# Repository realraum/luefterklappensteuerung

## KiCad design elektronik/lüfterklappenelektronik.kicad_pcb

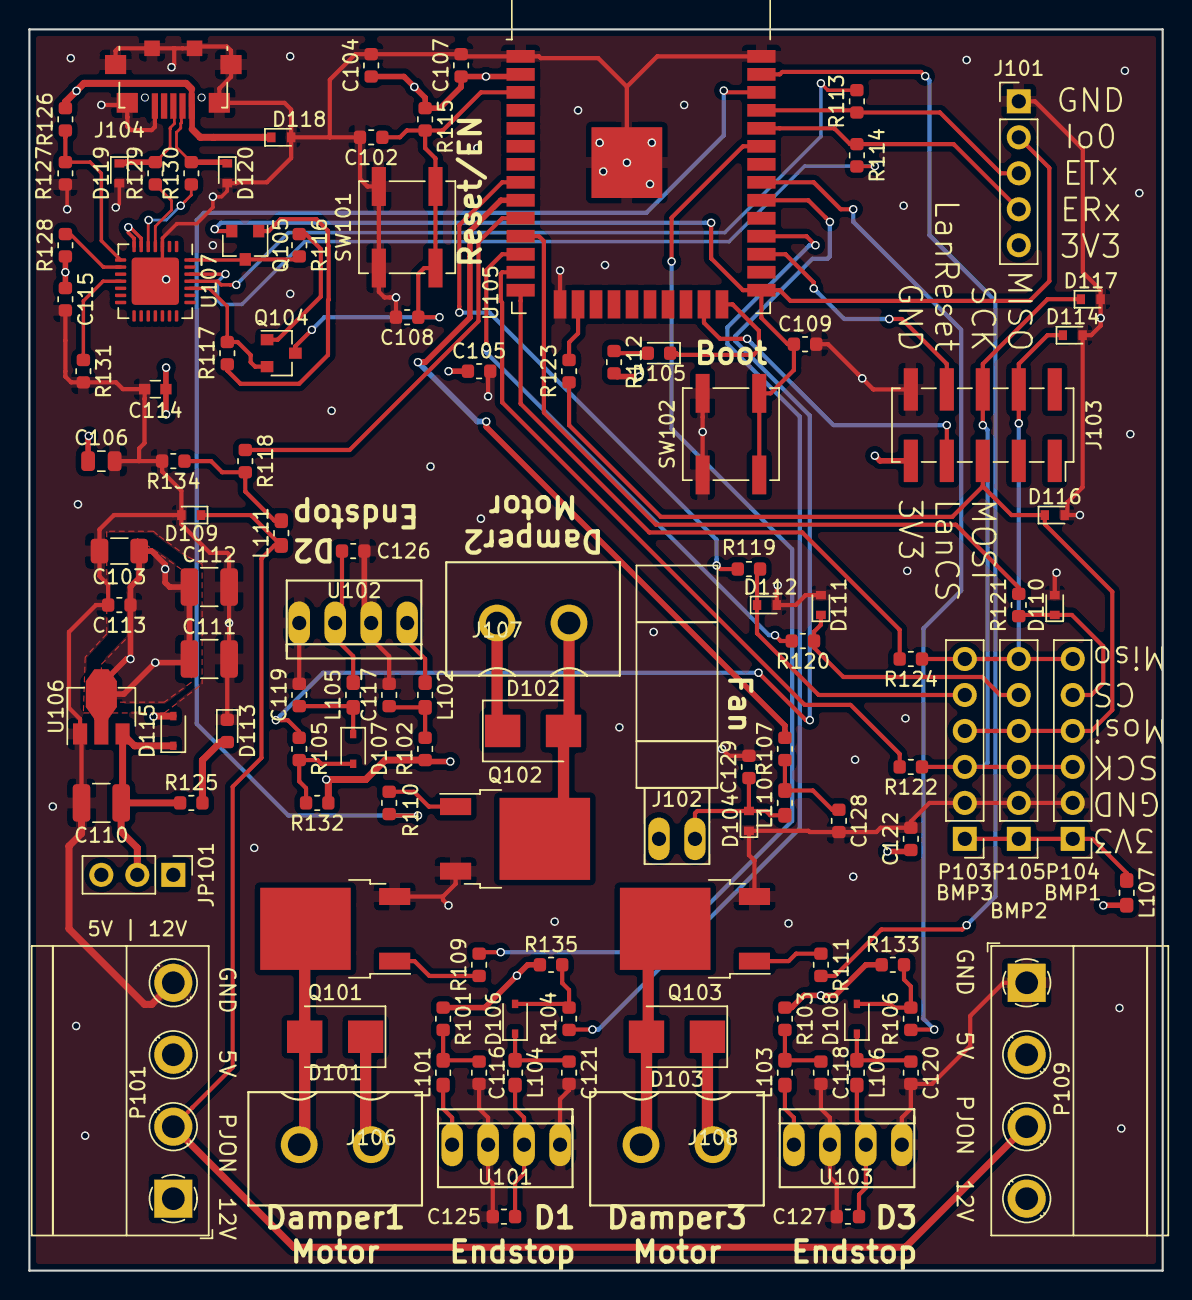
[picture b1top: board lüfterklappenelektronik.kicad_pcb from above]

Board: 4 copper layers, 80.0 x 87.6 mm, 115 parts (0 on the bottom side), 74 nets.

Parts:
C102, C104, C107, C108, C109, C113, C115: 100nF/50V; C_0603_1608Metric
C103: 220µF/6.3V(20%); C_1206_3216Metric
C105: 1µF/50V; C_0603_1608Metric
C106: 10µF/25V; C_0805_2012Metric
C110, C111, C112: 22uF/25V(10%); C_1210_3225Metric
C114: 4.7µF/6.3V(10%); C_0603
C116: 100pF; C_0603_1608Metric
C117, C118, C119, C120, C121, C122, C125, C126, C127, C128, C129: 100P; C_0603_1608Metric
D101, D102, D103: D_Schottky; D_SMB
D104, D109, D110, D111, D112, D114, D116, D117, D118, D119, D120: LESD5D5.0CT1G; D_SOD-523
D105, D113: GREEN_LED; LED_0603_1608Metric
D106, D107, D108, D115: BAT760-7; D_SOD-323
J101: Conn_01x05_Male; PinHeader_1x05_P2.54mm_Vertical
J102: Ckmtw_2510S-2P; C30436_pinhead_1x2_vertical_P2.54
J103: Conn_LAN_ENC28J60; PinSocket_2x05_P2.54mm_Vertical_SMD
J104: USB_B_Micro; USB_Micro-B_C77238
J106, J107, J108: WJ2EDGVC-5.08-2P
JP101: Jumper µC Supply; PinHeader_1x03_P2.54mm_Vertical
L101, L102, L103, L104, L105, L106, L107, L110, L111: GZ1608D222TF; L_0603_1608Metric_Pad1.05x0.95mm_HandSolder
P101, P109: PWR_BUS_CONN; WJ2EDGRC-5.08-4P
P103: PressureSensor3; PinHeader_1x06_P2.54mm_Vertical
P104: PressureSensor1; PinHeader_1x06_P2.54mm_Vertical
P105: PressureSensor2; PinHeader_1x06_P2.54mm_Vertical
Q101, Q102, Q103: IRLR8743TRPBF; TO-252-2
Q104, Q105: Q_NPN_Darlington_BEC; SOT-23
R101, R102, R103, R109, R110, R111: 91(1%); R_0603_1608Metric
R104, R105, R106, R132, R133, R135: 5K6(1%); R_0603_1608Metric
R107: 160(1%); R_0603_1608Metric
R112: 110(1%); R_0603_1608Metric
R113, R114: 0R(5%); R_0603_1608Metric
R115, R116, R117, R131, R134: 10K(5%); R_0603_1608Metric
R118, R119, R120, R121: 220(1%); R_0603_1608Metric
R122, R123, R124, R129, R130: 22(1%); R_0603_1608Metric
R125, R128: 2K(5%); R_0603_1608Metric
R126: 22.1K(5%); R_0603_1608Metric
R127: 47.5K(5%); R_0603_1608Metric
SW101, SW102: SW_Push; SW_SPST_B3SL-1022P
U101, U102, U103: Gabellichtschranke; Ckmtw_2510S-4P
U105: ESP32-WROOM-32E; ESP32-WROOM-32
U106: AMS1117-3.3; SOT-89-3
U107: CP2102N-A01-GQFN28; QFN-28-1EP_5x5mm_P0.5mm_EP3.35x3.35mm

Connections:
+3V3: C103.1, C104.1, C105.1, C106.1, C107.1, C111.1, C112.1, C113.1, C114.1, C115.1, C122.1, J101.5, J102.1, J103.9, L107.2, R101.1, R102.1, R103.1, R112.2, R115.1, R128.1, R132.1, R133.1, R135.1, U105.2, U106.2, U107.6, U107.7
+5V: JP101.3, P101.3, P109.2
+12V: D101.1, D102.1, D103.1, J106.1, J107.1, J108.1, JP101.1, P101.1, P109.4
+VDC: C110.1, D115.1, JP101.2, R125.1, U106.3
/DTR: Q105.3, R116.2, U107.28
/Damper1: R109.2, U105.33
/Damper2: R110.2, U105.36
/Damper3: R111.2, U105.37
/ESP_EN: C102.1, C108.1, Q104.3, R115.2, SW101.2, U105.3
/EndstopDamper1: R104.1, U105.28
/EndstopDamper2: R105.1, U105.30
/EndstopDamper3: R106.1, U105.31
/FAN: R107.2, U105.9
/IO0: C109.1, J101.2, Q105.2, SW102.2, U105.25
/LAN_CS: J103.7, U105.23
/LAN_RESET: J103.8, U105.27
/MISO: D114.1, J103.4, P103.6, P104.6, P105.6, R124.1
/MOSI: D116.1, J103.5, P103.4, P104.4, P105.4, R123.1
/ONBOARD_LED: D105.1, U105.24
/PJON: D109.1, L111.1, P101.2, P109.3
/PS1_CS: D110.1, P104.5, R121.1
/PS2_CS: D111.1, P105.5, R120.1
/PS3_CS: D112.1, P103.5, R119.1
/RTS: Q104.2, R117.2, U107.24
/RXD: R113.2, U107.25
/RXD0: J101.4, R114.1, U105.34
/SCK: D117.1, J103.6, P103.3, P104.3, P105.3, R122.1
/TXD: R114.2, U107.26
/TXD0: J101.3, R113.1, U105.35
/UCD+: D119.1, J104.3, R129.2
/UCD-: D120.1, J104.2, R130.2
/USB_D+: R129.1, U107.4
/USB_D-: R130.1, U107.5
/VBUS: D115.2, D118.1, J104.1, R126.2
GND: C102.2, C103.2, C104.2, C105.2, C106.2, C107.2, C108.2, C109.2, C110.2, C111.2, C112.2, C113.2, C114.2, C115.2, C116.2, C117.2, C118.2, C119.2, C120.2, C121.2, C122.2, C125.2, C126.2, C127.2, C128.2, C129.2, D104.1, D109.2, D110.2, D111.2, D112.2, D113.1, D114.2, D116.2, D117.2, D118.2, D119.2, D120.2, J101.1, J103.10, J104.5, J104.6, P101.4, P103.2, P104.2, P105.2, P109.1, Q101.3, Q102.3, Q103.3, R127.2, R131.2, R134.2, SW101.1, SW102.1, U101.2, U101.4, U102.2, U102.4, U103.2, U103.4, U105.1, U105.15, U105.38, U105.39, U106.1, U107.3, U107.29
unnamed: C116.1, L101.2, R101.2
unnamed: C117.1, L102.2, R102.2
unnamed: C118.1, L103.2, R103.2
unnamed: C119.1, D107.1, L105.1
unnamed: C120.1, D108.1, L106.1
unnamed: C121.1, D106.1, L104.1
unnamed: C125.1, L104.2, U101.3
unnamed: C126.1, L105.2, U102.3
unnamed: C127.1, L106.2, U103.3
unnamed: C128.1, L110.2, R107.1
unnamed: C129.1, D104.2, J102.2, L110.1
unnamed: D101.2, J106.2, Q101.2
unnamed: D102.2, J107.2, Q102.2
unnamed: D103.2, J108.2, Q103.2
unnamed: D105.2, R112.1
unnamed: D106.2, R104.2, R135.2
unnamed: D107.2, R105.2, R132.2
unnamed: D108.2, R106.2, R133.2
unnamed: D113.2, R125.2
unnamed: L101.1, U101.1
unnamed: L102.1, U102.1
unnamed: L103.1, U103.1
unnamed: L107.1, P103.1, P104.1, P105.1
unnamed: L111.2, R118.2, R134.1
unnamed: Q101.1, R109.1
unnamed: Q102.1, R110.1
unnamed: Q103.1, R111.1
unnamed: Q104.1, R116.1
unnamed: Q105.1, R117.1
unnamed: R118.1, U105.10
unnamed: R119.2, U105.8
unnamed: R120.2, U105.12
unnamed: R121.2, U105.11
unnamed: R122.2, U105.13
unnamed: R123.2, U105.16
unnamed: R124.2, U105.14
unnamed: R126.1, R127.1, U107.8
unnamed: R128.2, U107.9
unnamed: R131.1, U107.11

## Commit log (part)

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2021-02-14 update settings code
2021-03-21 usb d- d+ bugfix
2025-12-02 Bump github.com/eclipse/paho.mqtt.golang in /ventilationinterface
    Bumps [github.com/eclipse/paho.mqtt.golang](https://github.com/eclipse/paho.mqtt.golang) from 1.3.5 to 1.5.1.
    - [Release notes](https://github.com/eclipse/paho.mqtt.golang/releases)
    - [Commits](https://github.com/eclipse/paho.mqtt.golang/compare/v1.3.5...v1.5.1)
    ---
    updated-dependencies:
    - dependency-name: github.com/eclipse/paho.mqtt.golang
2026-05-07 corr
2026-05-07 custom calibration
2026-05-07 raspios changes bugfixes
2026-05-07 now a system service since linger no longer works without boot
2026-05-07 gomodules
2026-05-07 pins
2026-05-07 closer to working X
2026-05-07 naive homeassistant controlled ventilation pcb
